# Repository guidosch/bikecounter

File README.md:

# BikeCounter  <!-- omit in toc -->

This repository contains the hardware and software components of a [PIR](https://en.wikipedia.org/wiki/Passive_infrared_sensor) based tracking device to monitor the usage of local bike trails. The data is sent over [LoRaWAN](https://de.wikipedia.org/wiki/Long_Range_Wide_Area_Network) to [TTN](https://www.thethingsnetwork.org/) and from there to a [Google Cloud](https://console.cloud.google.com) backend which stores the data and provides api endpoints for the data visualization web UI ([bikeCounterUI](https://github.com/guidosch/bikecounterUI)).

The repository is divided into two main sections. The first one contains all the data regarding the hardware components and the second one holds the software code.

- [Hardware](#hardware)
- [Software](#software)
  - [Overview](#overview)
  - [BikeCounter](#bikecounter)
    - [Overall state machine](#overall-state-machine)
    - [Data package](#data-package)
    - [Time scheduler](#time-scheduler)
    - [Device configuration](#device-configuration)
    - [Unit tests](#unit-tests)
    - [To be aware of](#to-be-aware-of)
  - [TTN](#ttn)
  - [Google Cloud](#google-cloud)
- [Contributing](#contributing)
- [License](#license)

# Hardware

The core component of the device is an [Arduino MRKWAN 1310](https://docs.arduino.cc/hardware/mkr-wan-1310) which sits on the "logic layer" PCB. This PCB connects the micro controller to the sensors, the dip switches and the "power layer" PCB.

To detect the movement a PIR sensor from [Seeed Studio](https://www.seeedstudio.com/Grove-PIR-Motion-Sensor.html) is used and to monitor the internal environment of the device a temperature and humidity sensor from [Adafruit](https://www.adafruit.com/product/3721) was chosen.

The "power layer" PCB holds two rechargeable lithium-ion batteries (18650). This allows the device to run up to one year without exchanging the batteries.

The schematics and layout files of the PCBs as well as the BOM of the whole device can be found in the corresponding subfolder.

# Software

This Repository contains the code for the tracking device as well as the scripts running on the backend.

## Overview

```mermaid
flowchart LR;
  subgraph BikeCounter;
    Biker(Round) -->|infrared radiation| PIR-sensor;
    PIR-sensor -->|DIO| Arduino-MKRWAN-1310;
    Temp&Hum-sensor -->|I2C| Arduino-MKRWAN-1310;
    DIP-switches -->|DIO| Arduino-MKRWAN-1310;
  end; 
  subgraph TTN;   
    Arduino-MKRWAN-1310 -->|LoRaWAN| PayloadFormatter;
  end;  
  subgraph Google Cloud;
    PayloadFormatter -->|webhook| Cloud-function;
    Cloud-function --> firebase;
  end;
```

## BikeCounter

There are two versions of the main BikeCounter software. The **light** version is a simple and basic implementation of the needed functionality. The **pro** version has extended features that allow it to take track of time as well as its environnement conditions.

(Due to the fact that the light version is almost obsolete only the pro version will be explained in more detail.)

### Overall state machine

```mermaid
stateDiagram-v2
    m1: main loop
    [*] --> Setup
    Setup --> m1
    state m1 {
      state if_motion <<choice>>
      s0: motion detected ?
      s1: store information in variable      
      s2: timer called
      s3: threshold reached ?
      state if_threshold <<choice>>
      s4: send data
      state if_downlink <<choice>>
      s5: downlink received ?
      s6: correct rtc drift
      
      [*] --> s0
      s0 --> if_motion
      if_motion --> s1: true
      if_motion --> s2: false
      s2 --> s4
      s1 --> s3
      s3 --> if_threshold
      if_threshold --> deepSleep: false
      if_threshold --> s4: true
      s4 --> s5
      s5 --> if_downlink
      if_downlink --> deepSleep: false
      if_downlink --> s6: true
      s6 --> deepSleep
      deepSleep --> [*]
    }
```

After the main loop finishes the device goes into a deepSleep mode. From there the PIR sensor or the rtc timer can wake it back up and trigger the main loop again.

### Data package

The payload size of one single LoRaWAN data package is restricted to 51 bytes. To avoid multi-package messages and to reduce transmission time an optimized information transmission protocol was developed.

The dataPackage class handles all the information conversion and encoding. A detailed documentation of the protocol can be found in the dataPackage.xlsx file.

**Payload encoding**

| address<br>bits | 0-7<br>[8] | 8-11<br>[4]      | 12-15<br>[4]     | 16-18<br>[3] | 19-23<br>[5]    | 24-27<br>[5] | 28-30<br>[3] | 31-54<br>[24] | 55-57<br>[3]   | 58-62<br>[5]    | 63-408<br>[6/7/8/9/10] |
| --------------- | ---------- | ---------------- | ---------------- | ------------ | --------------- | ------------ | ------------ | ------------- | -------------- | --------------- | ---------------------- |
| **content**     | count      | software version | hardware version | status index | battery voltage | temperature  | humidity     | device time   | interval index | hour of the day | offset minutes array   |

The data type size of the offset array depends on the selected interval.

### Time scheduler

During the night as well as the cold seasons of the year the data transmission interval can be adjusted to save energy and transmission time. The timeScheduler class provides all the necessary methods to accomplish such a dynamic behavior.

### Device configuration

The configuration information to establish a connection to the TTN (AppEUI and AppKey) is saved to the flash memory of the Arduino MKRWAN 1310. The `writeConfigToFlash.ino` script saves a new configuration to the memory.

### Unit tests

This repository contains serval unit tests for the dataPackage and the timeScheduler class. The tests are written using the [Google Test](https://google.github.io/googletest/) framework. A cMake configuration for local testing is provided as well as an automated CI pipeline for the master branch. The `runTestsLocal.sh` script executes all the commands needed to run the unit tests locally.

### To be aware of

- The LoRa module is very timing sensitive. That is the reason there are so many delays in the code to give it enough time to wait for messages and to response.

- The first time the (deep)sleep method is called, it re-initializes the RTC to a wrong value. To fix this issue the first iteration of the main loop puts the device into the sleep mode for a short period of time and resets the RTC in the next loop.

## TTN

The message from the device gets over LoRaWAN to the TTN server where a uplink payload formatter parses the data bytes to a human readable JavaScript object. The server then triggers a webhook and passes the data object to the Google Cloud function API endpoint.

The downlink message with the time drift information will also be parsed by the payload formatter defined in TTN.

The up/down-link payload formatter scripts are stored in the TTN subfolder.

## Google Cloud

The triggered cloud function evaluates the data object sent from TTN and saves it to the Firebase database. Depending on the difference between the local time of the device and the server time it schedules a downlink message to correct the internal device time.

There are also cloud functions that provide an API endpoint for the web UI ([bikeCounterUI](https://github.com/guidosch/bikecounterUI)) to visualize the stored data.

# Setup IDE and compile code
Download and install: `arduino-cli` which is available for brew or apt-get. Install the `arduino` extension for VSCode and adjust the `arduino.path` in the extension settings and point to your arduino-cli installation folder.

Add the following libraries to your installation: `arduino-cli lib install [libName]`

- Needed libraries:
  - MKRWAN@1.1.0
  - RTCZero@1.6.0
  - SPI.h --> already preinstalled
  - SparkFun SPI SerialFlash Arduino Library@1.0.3
  - Arduino Low Power@1.2.2
  - Adafruit Unified Sensor@1.1.6

Copy and adjust the `.vscode/c_cpp_properties.json_example` for your platform. You have to adjust the place where arduino-cli downloads the libraries as they are needed by the IDE

Compile: `arduino-cli compile --fqbn arduino:samd:mkrwan1310 BikeCounterPro.ino`

Deploy: `arduino-cli upload -p [/dev/yourdevice] --fqbn arduino:samd:mkrwan1310 BikeCounterPro.ino`

Hint: `arduino-cli board list` will show the USB port, where the device is connected

# Contributing

Pull requests are welcome. For major changes, please open an issue first to discuss what you would like to change.

Please make sure to update the tests as appropriate.

# License

This project is licensed under [CC0-1.0](LICENSE)

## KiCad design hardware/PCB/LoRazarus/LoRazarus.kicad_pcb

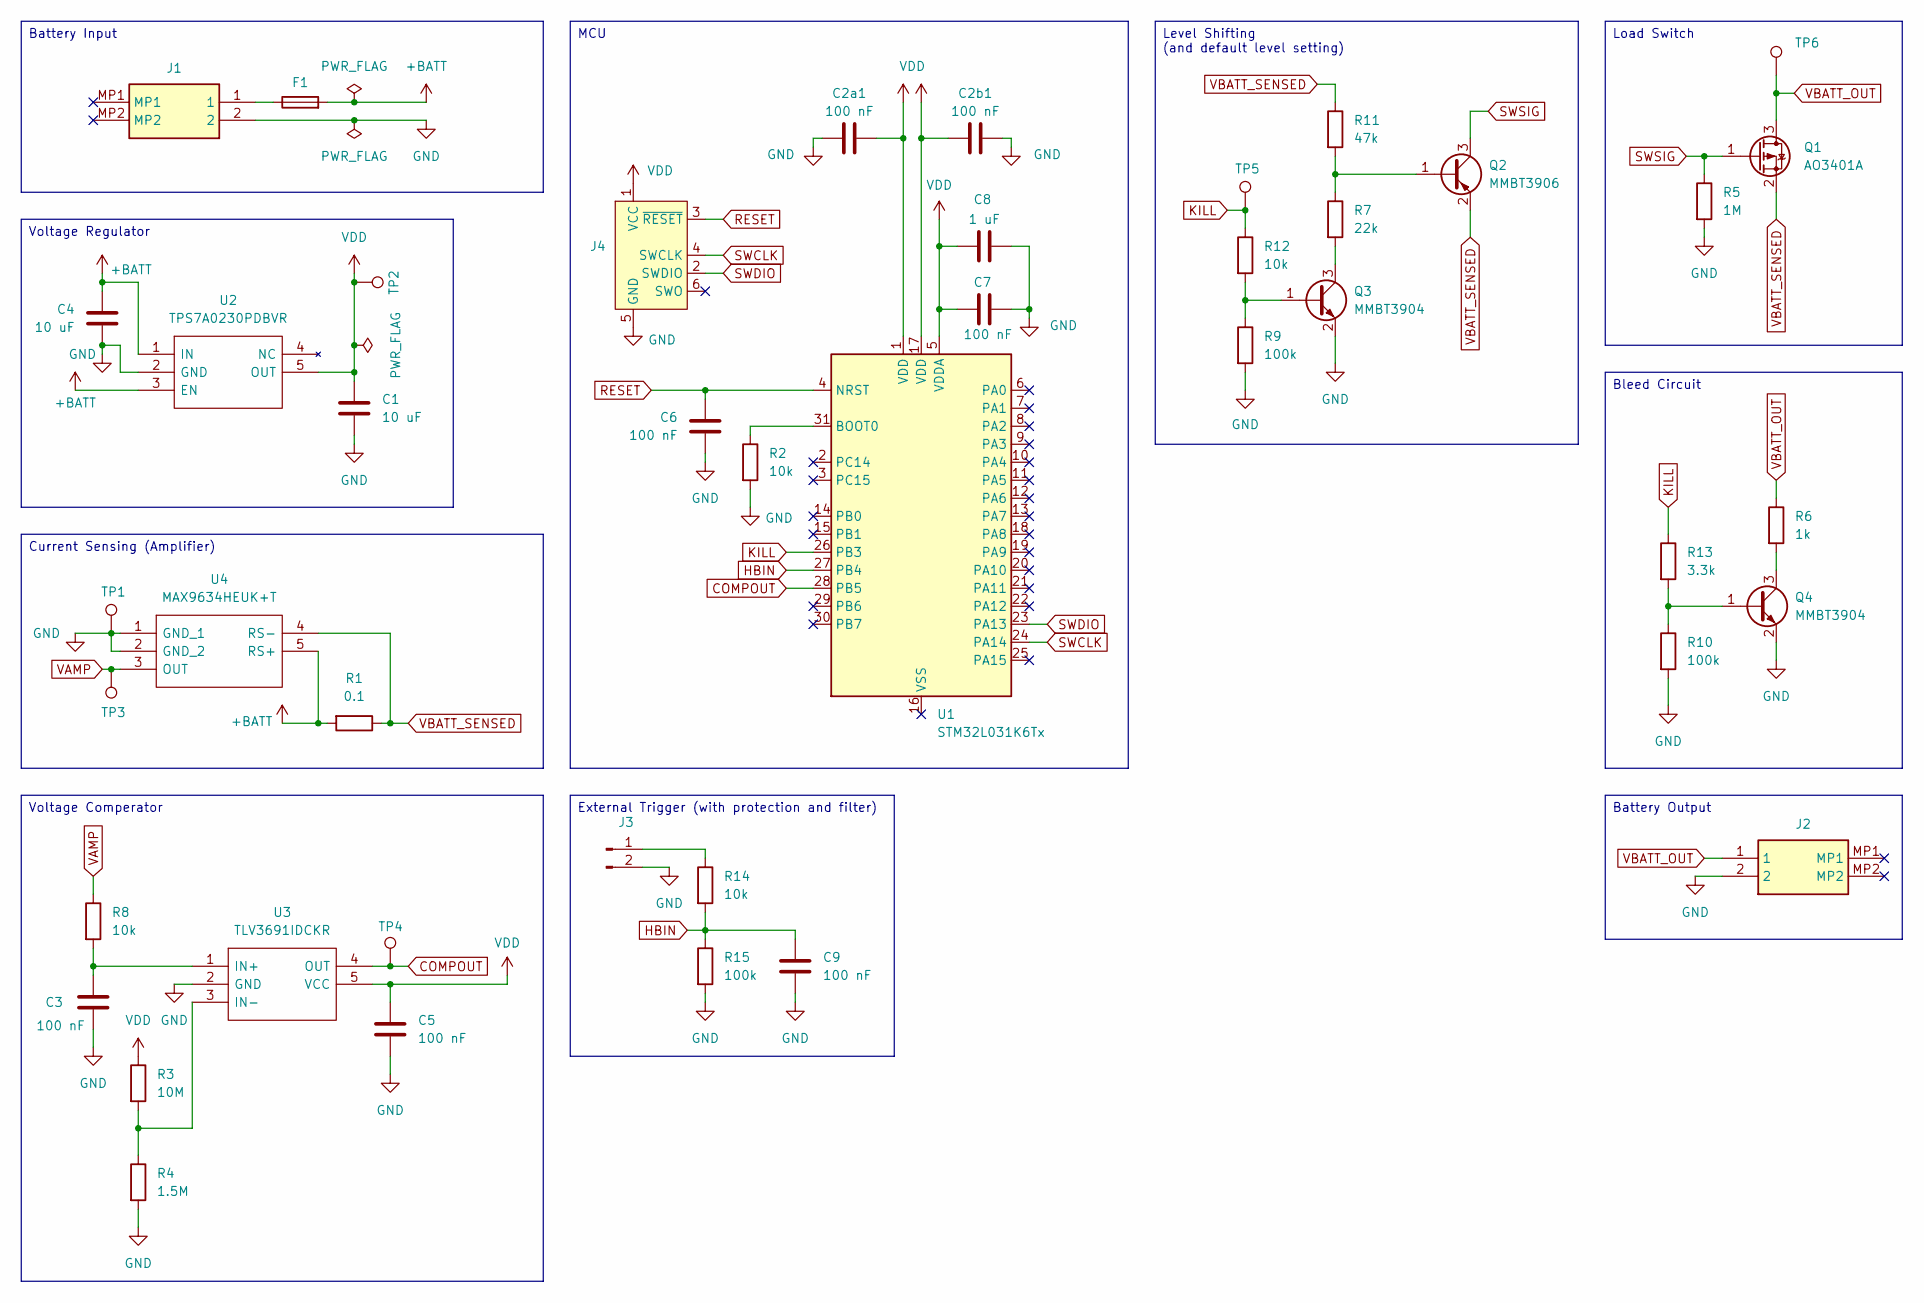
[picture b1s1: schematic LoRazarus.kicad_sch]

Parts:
C1, C4: 10 uF; C_0805_2012Metric
C2a1, C2b1, C3, C5, C6, C7, C9: 100 nF; C_0603_1608Metric
C8: 1 uF; C_0603_1608Metric
F1: Fuse; Fuse_1206_3216Metric
J1, J2: S2B-PH-SM4-TB_LF__SN_; S2BPHSM4TBLFSN; Mouser Part Number N/A
J3: Conn_01x02_Pin; PinHeader_1x02_P2.54mm_Vertical
J4: Conn_ARM_SWD_TagConnect_TC2030-NL; Tag-Connect_TC2030-IDC-NL_2x03_P1.27mm_Vertical
Q1: AO3401A; SOT-23
Q2: MMBT3906; SOT-23
Q3, Q4: MMBT3904; SOT-23
R1: 0.1; R_1206_3216Metric
R2, R8, R12, R14: 10k; R_0603_1608Metric
R3: 10M; R_0603_1608Metric
R4: 1.5M; R_0603_1608Metric
R5: 1M; R_0603_1608Metric
R6: 1k; R_0603_1608Metric
R7: 22k; R_0603_1608Metric
R9, R10, R15: 100k; R_0603_1608Metric
R11: 47k; R_0603_1608Metric
R13: 3.3k; R_0603_1608Metric
TP1, TP2, TP3, TP4, TP5, TP6: TestPoint; TestPoint_Pad_1.0x1.0mm
U1: STM32L031K6Tx; LQFP-32_7x7mm_P0.8mm
U2: TPS7A0230PDBVR; SOT-23-5; Mouser Part Number 595-TPS7A0230PDBVR
U3: TLV3691IDCKR; SOT-353_SC-70-5; Mouser Part Number 595-TLV3691IDCKR
U4: MAX9634HEUK+T; SOT-23-5; Mouser Part Number 700-MAX9634HEUKT

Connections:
+BATT: C4.1, F1.2, R1.2, U2.1 (IN), U2.3 (EN), U4.5 (RS+)
COMPOUT: TP4.1 (1_1), U1.28 (PB5), U3.4 (OUT)
GND: C1.2, C2a1.2, C2b1.2, C3.2, C4.2, C5.2, C6.2, C7.2, C8.2, C9.2, J1.2, J2.2, J3.2, J4.5 (GND), Q3.2 (E), Q4.2 (E), R2.2, R4.2, R5.2, R9.2, R10.2, R15.2, TP1.1 (1_1), U2.2 (GND), U3.2 (GND), U4.1 (GND_1), U4.2 (GND_2)
HBIN: C9.1, R14.2, R15.1, U1.27 (PB4)
KILL: R12.1, R13.1, TP5.1 (1_1), U1.26 (PB3)
unnamed: F1.1, J1.1
unnamed: J3.1, R14.1
unnamed: Q2.1 (B), R7.1, R11.2
unnamed: Q3.1 (B), R9.1, R12.2
unnamed: Q3.3 (C), R7.2
unnamed: Q4.1 (B), R10.1, R13.2
unnamed: Q4.3 (C), R6.2
unnamed: R2.1, U1.31 (BOOT0)
unnamed: C3.1, R8.2, U3.1 (IN+)
unnamed: R3.2, R4.1, U3.3 (IN-)
RESET: C6.1, J4.3 (~RESET), U1.4 (NRST)
SWCLK: J4.4 (SWCLK), U1.24 (PA14)
SWDIO: J4.2 (SWDIO), U1.23 (PA13)
SWSIG: Q1.1 (G), Q2.3 (C), R5.1
VAMP: R8.1, TP3.1 (1_1), U4.3 (OUT)
VBATT_OUT: J2.1, Q1.3 (D), R6.1, TP6.1 (1_1)
VBATT_SENSED: Q1.2 (S), Q2.2 (E), R1.1, R11.1, U4.4 (RS-)
VDD: C1.1, C2a1.1, C2b1.1, C5.1, C7.1, C8.1, J4.1 (VCC), R3.1, TP2.1 (1_1), U1.1 (VDD), U1.5 (VDDA), U1.17 (VDD), U2.5 (OUT), U3.5 (VCC)

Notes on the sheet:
Battery Input
External Trigger (with protection and filter)
Battery Output
Load Switch
Voltage Regulator
Level Shifting (and default level setting)
Current Sensing (Amplifier)
MCU
Bleed Circuit
Voltage Comperator

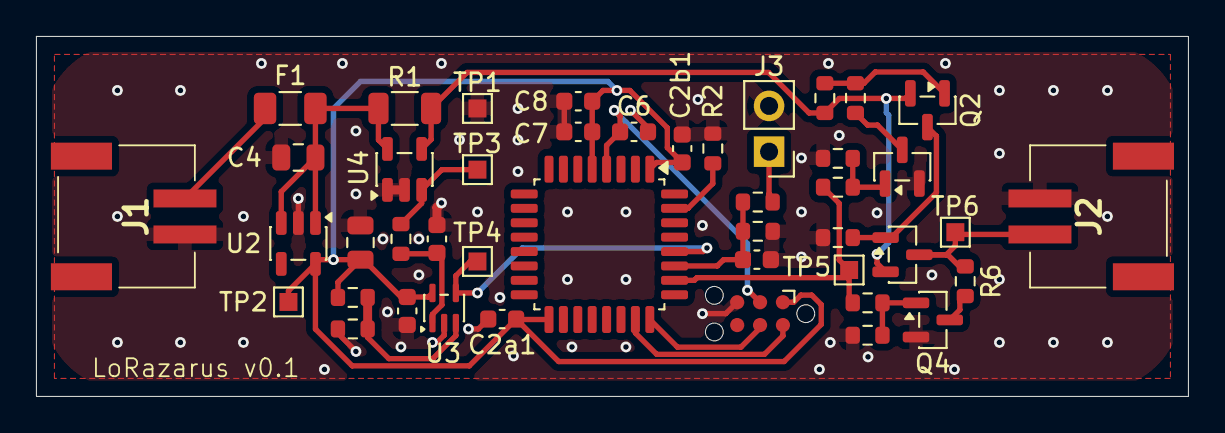
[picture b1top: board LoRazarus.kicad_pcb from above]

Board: 2 copper layers, 64.0 x 20.0 mm, 44 parts (0 on the bottom side), 23 nets.

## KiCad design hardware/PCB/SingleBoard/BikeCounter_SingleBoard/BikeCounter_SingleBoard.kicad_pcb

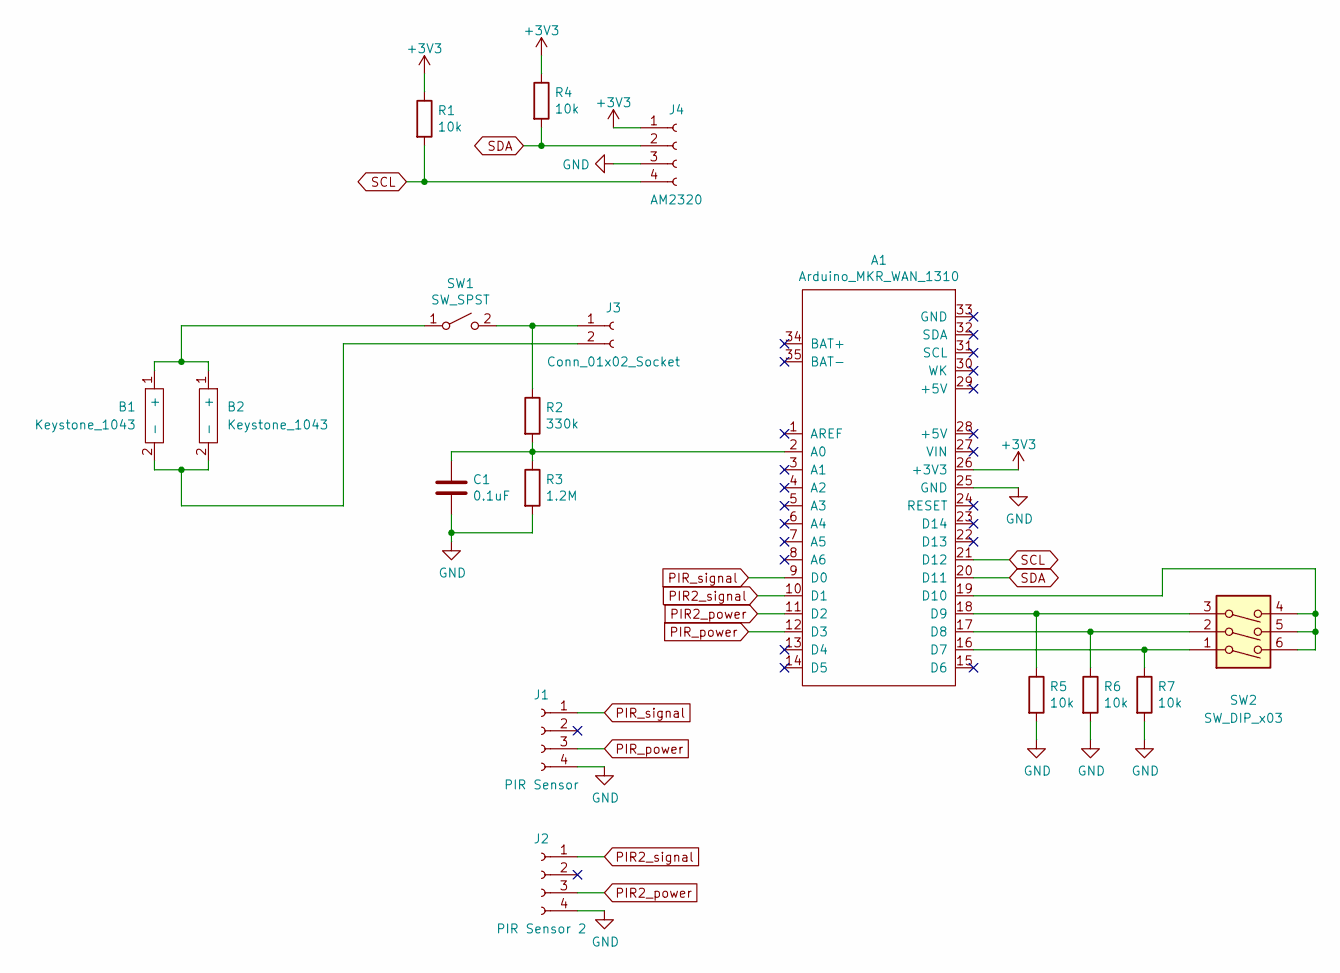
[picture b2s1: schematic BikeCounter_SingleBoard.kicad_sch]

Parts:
A1: Arduino_MKR_WAN_1310
B1, B2: Keystone_1043; BatteryHolder_Keystone_1043_1x18650
C1: 0.1uF; C_0805_2012Metric_Pad1.18x1.45mm_HandSolder
J1: PIR Sensor; PinSocket_1x04_P2.00mm_Vertical
J2: PIR Sensor 2; PinSocket_1x04_P2.00mm_Vertical
J3: Conn_01x02_Socket; PinSocket_1x02_P2.54mm_Vertical
J4: AM2320; PinSocket_1x04_P2.54mm_Vertical
R1, R4, R5, R6, R7: 10k; R_1206_3216Metric_Pad1.30x1.75mm_HandSolder
R2: 330k; R_1206_3216Metric_Pad1.30x1.75mm_HandSolder
R3: 1.2M; R_1206_3216Metric_Pad1.30x1.75mm_HandSolder
SW1: SW_SPST; Switch_MHS12204
SW2: SW_DIP_x03; SW_DIP_SPSTx03_Slide_6.7x9.18mm_W8.61mm_P2.54mm_LowProfile

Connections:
+3V3: A1.26 (+3V3), J4.1, R1.1, R4.1
GND: A1.25 (GND), C1.2, J1.4, J2.4, J4.3, R3.2, R5.2, R6.2, R7.2
unnamed: A1.2 (A0), C1.1, R2.2, R3.1
unnamed: A1.16 (D7), R7.1, SW2.1
unnamed: A1.17 (D8), R6.1, SW2.2
unnamed: A1.18 (D9), R5.1, SW2.3
unnamed: A1.19 (D10), SW2.4, SW2.5, SW2.6
unnamed: B1.1 (+), B2.1 (+), SW1.1 (A)
unnamed: B1.2 (-), B2.2 (-), J3.2
unnamed: J3.1, R2.1, SW1.2 (B)
PIR2_power: A1.11 (D2), J2.3
PIR2_signal: A1.10 (D1), J2.1
PIR_power: A1.12 (D3), J1.3
PIR_signal: A1.9 (D0), J1.1
SCL: A1.21 (D12), J4.4, R1.2
SDA: A1.20 (D11), J4.2, R4.2

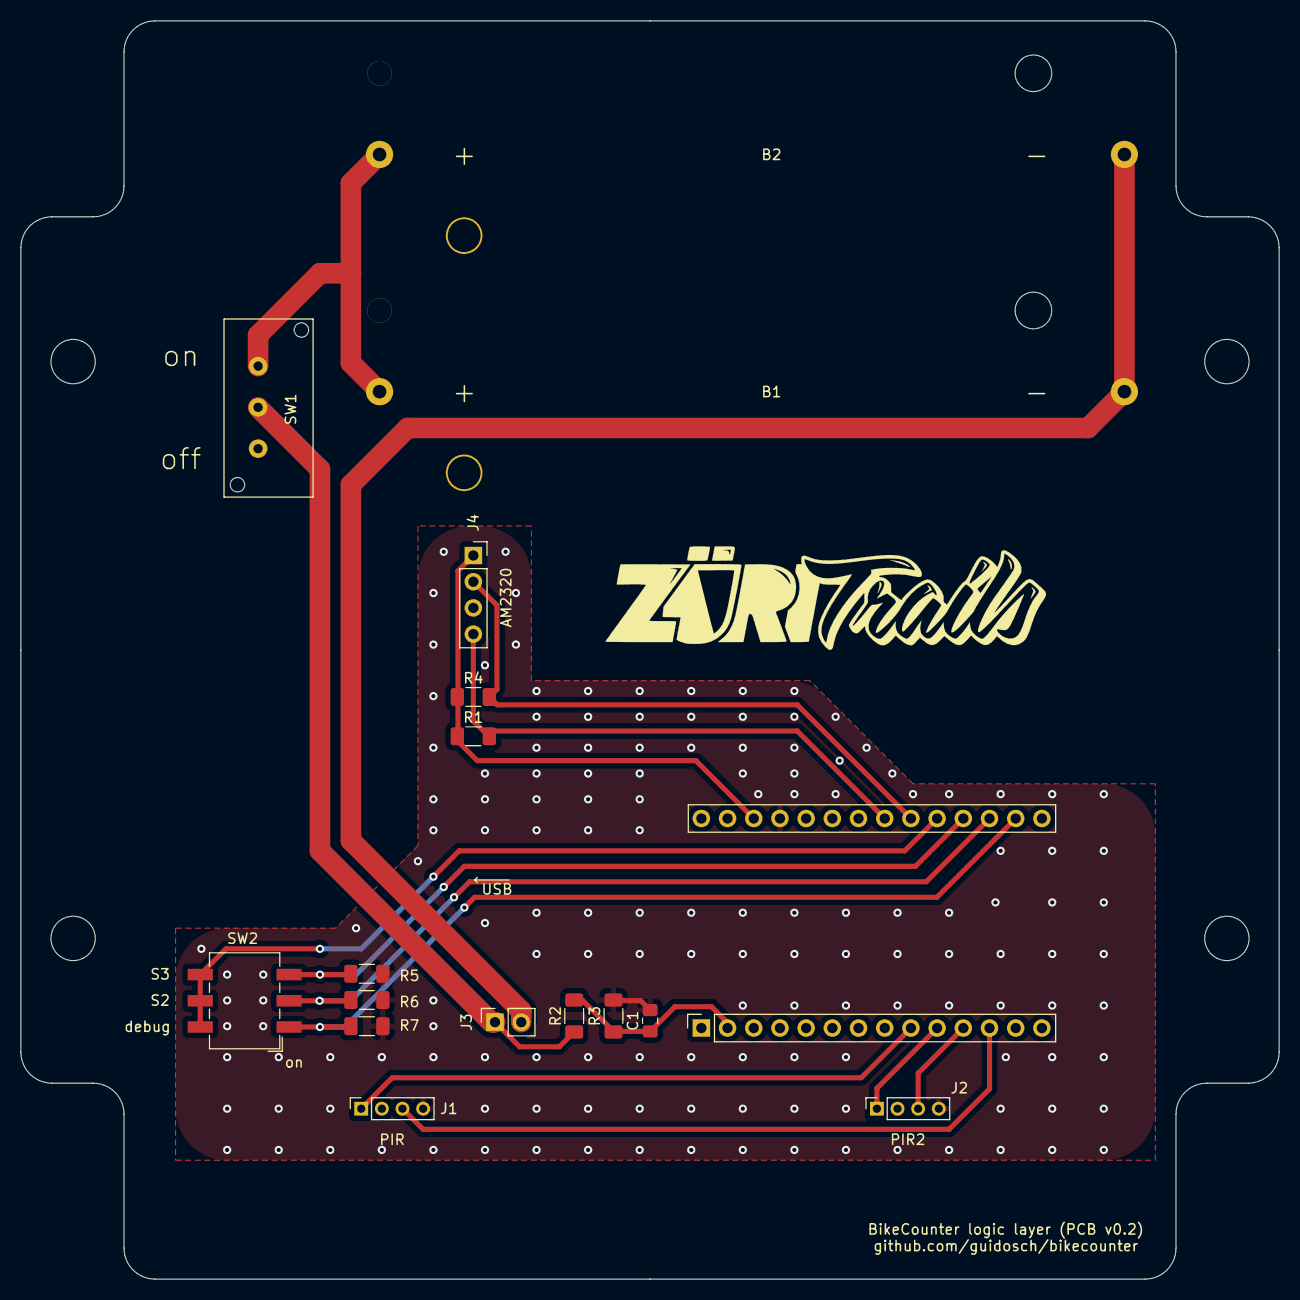
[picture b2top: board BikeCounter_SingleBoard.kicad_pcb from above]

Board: 2 copper layers, 122.0 x 122.0 mm, 17 parts (0 on the bottom side), 16 nets.

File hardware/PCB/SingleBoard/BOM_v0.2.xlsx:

Id | Designator | Package | Quantity | Designation | Price |  | Link 1 | Link 2 | Link 3
1 |  | PCB | 1 | JLC PCB (20 Stk.) | 3.5590000000000002 | 3.5590000000000002
2 | A1 | Arduino_MKR_WAN_1310 | 1 | Arduino_MKR_WAN_1310 | 39.44 | 39.44 | https://www.mouser.ch/ProductDetail/Arduino/ABX00029?qs=rkhj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
3 | B1,B2 | BatteryHolder_Keystone_1043_1x18650 | 2 |  | 2.15 | 4.3 | https://www.mouser.ch/ProductDetail/Keystone-Electronics/104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
 | C1 | Capacitor_SMD:C_0805_2012Metric_Pad1.18x1.45mm_HandSolder | 2 | 0.1uF | 5.6000000000000001E-2 | 0.112 | https://www.mouser.ch/ProductDetail/KEMET/C0805C104K5RAC7411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 | https://www.mouser.ch/ProductDetail/Murata-Electronics/GCJ31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
 | R1,R4,R5,R6,R7 | Resistor_SMD:R_1206_3216Metric_Pad1.30x1.75mm_HandSolder | 5 | 10k | 0.186 | 0.92999999999999994 | https://www.mouser.ch/ProductDetail/Bourns/CHP1206AFX-1002EL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
 | R2 | Resistor_SMD:R_1206_3216Metric_Pad1.30x1.75mm_HandSolder | 1 | 330k | 0.121 | 0.121 | https://www.mouser.ch/ProductDetail/Susumu/RG3216P-3303-D-T5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
 | R3 | Resistor_SMD:R_1206_3216Metric_Pad1.30x1.75mm_HandSolder | 1 | 1.2M | 0.14199999999999999 | 0.14199999999999999 | https://www.mouser.ch/ProductDetail/YAGEO/RT1206FRE071M2L?qs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
 | SW1 | General_TM:Switch_MHS12204 | 1 | SW_SPST | 0.72799999999999998 | 0.72799999999999998 | https://www.mouser.ch/ProductDetail/TE-Connectivity-Alcoswit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
 | SW2 | Button_Switch_SMD:SW_DIP_SPSTx03_Slide_6.7x9.18mm_W8.61mm_P2.54mm_LowProfile | 1 | SW_DIP_x03 | 0.51200000000000001 | 0.51200000000000001 | https://www.mouser.ch/ProductDetail/CTS-Electronic-Component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
 | J1,J2 | Connector_PinSocket_2.00mm:PinSocket_1x04_P2.00mm_Vertical | 2 | PIR, PIR 2 | 9.9000000000000005E-2 | 0.19800000000000001 | https://www.seeedstudio.com/Grove-Universal-4-pin-connector.html
 |  | PinSocket_1x14_P2.54mm_Vertical | 2 | Board connector | 1.93 | 3.86 | https://www.mouser.ch/ProductDetail/Harwin/M20-7821446?qs=Jp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
 |  | Grove PIR sensor | 1 |  | 7.06 | 7.06 | https://www.distrelec.ch/de/grove-pir-bewegungssensor-seeed-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
 |  | AM2320 | 1 |  | 6.65 | 6.65 | https://www.distrelec.ch/de/digitaler-temperatur-und-feuchti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
 |  | Antenne | 1 |  | 21.52 | 21.52 | https://www.mouser.ch/ProductDetail/712-ANT-8-9-SPNF2
 |  | Adapter | 1 |  | 15.23 | 15.23 | https://www.mouser.ch/ProductDetail/523-242114
 |  | Kabel | 1 |  | 8.1 | 8.1 | https://www.mouser.ch/ProductDetail/RF-Solutions/CBA-UFLSMA1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
 |  | Casing 135x135x60mm | 1 |  | 18.5 | 18.5 | https://www.distrelec.ch/de/kunststoffgehaeuse-mit-durchsich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
 |  | Schrauben M3.5 | 4 |  | 1.2500000000000001E-2 | 0.05 | https://www.distrelec.ch/de/kreuzschraube-flachkopf-blech-po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
 |  | Akku | 2 | 2.6Ah | 18.32 | 36.64 | https://www.distrelec.ch/de/akku-li-ion-18650-6v-6ah-ansmann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
 |  |  |  |  |  | 164.09300000000002
 |  | Akku alternative | 1 | 3.5Ah | 23.32 | 23.32 | https://www.distrelec.ch/de/akku-li-ion-18650-6v-5ah-ansmann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
 |  | Akku alternative | 1 | 3.4Ah (USB ladebuchse) | 21.9 | 21.9 | https://www.distrelec.ch/de/akku-mit-usb-ladebuchse-li-ion-1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
 |  |  |  | Aufstellung für 5 Stück | 746.96500000000015
 |  |  |  | Aufstellung für 10 Stück | 1567.4300000000003

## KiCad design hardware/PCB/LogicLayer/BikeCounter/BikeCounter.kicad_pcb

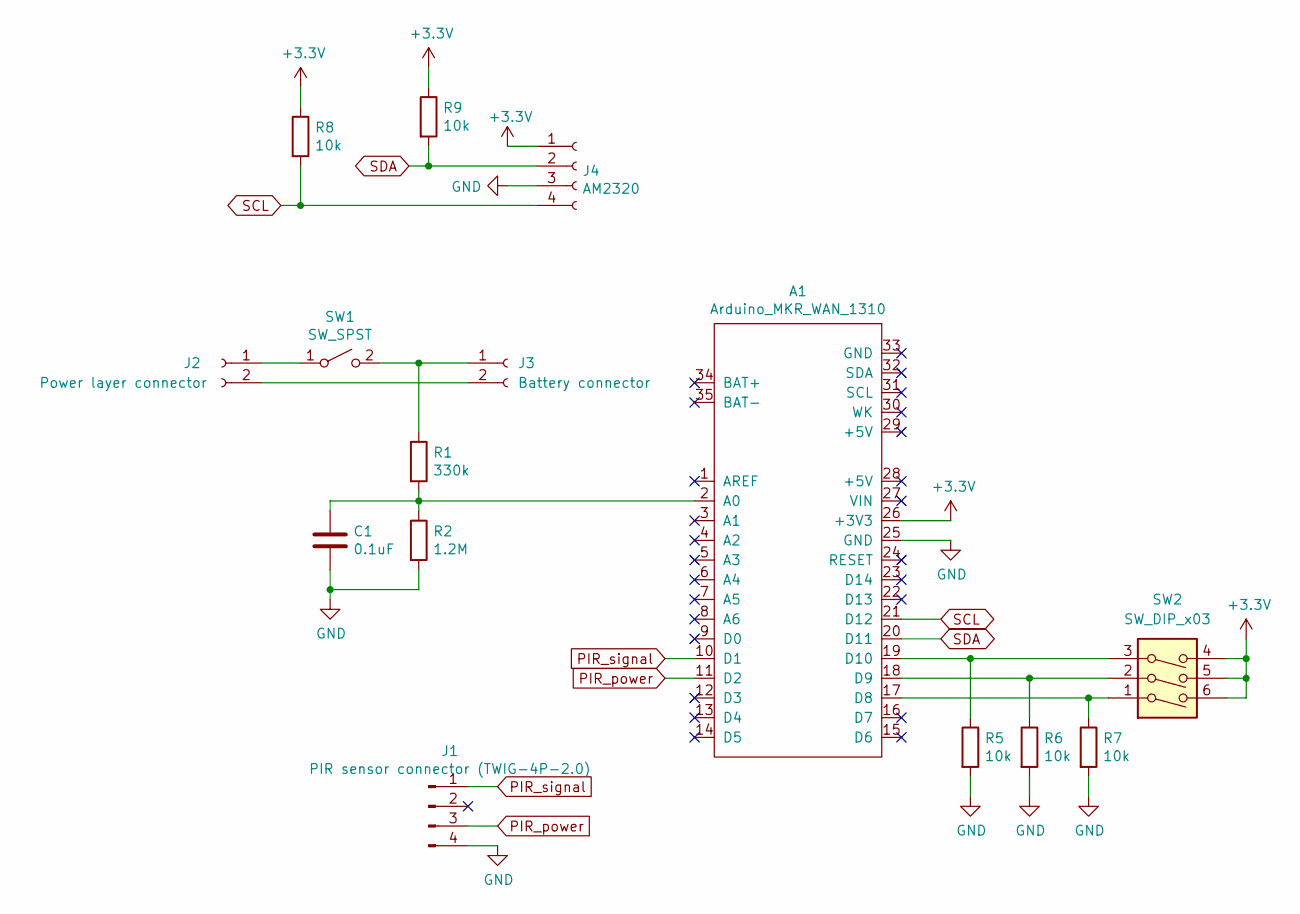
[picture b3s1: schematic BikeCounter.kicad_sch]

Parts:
A1: Arduino_MKR_WAN_1310
C1: 0.1uF; C_0805_2012Metric_Pad1.18x1.45mm_HandSolder
J1: PIR sensor connector (TWIG-4P-2.0); PinSocket_1x04_P2.00mm_Vertical
J2: Power layer connector; PinSocket_1x02_P2.54mm_Vertical
J3: Battery connector; PinSocket_1x02_P2.54mm_Vertical
J4: AM2320; PinSocket_1x04_P2.54mm_Vertical
R1: 330k; R_1206_3216Metric_Pad1.30x1.75mm_HandSolder
R2: 1.2M; R_1206_3216Metric_Pad1.30x1.75mm_HandSolder
R5, R6, R7, R8, R9: 10k; R_1206_3216Metric_Pad1.30x1.75mm_HandSolder
SW1: SW_SPST; Switch_MHS12204
SW2: SW_DIP_x03; SW_DIP_SPSTx03_Slide_6.7x9.18mm_W8.61mm_P2.54mm_LowProfile

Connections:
+3V3: A1.26 (+3V3), J4.1, R8.1, R9.1, SW2.4, SW2.5, SW2.6
GND: A1.25 (GND), C1.2, J1.4, J4.3, R2.2, R5.2, R6.2, R7.2
unnamed: A1.2 (A0), C1.1, R1.2, R2.1
unnamed: A1.17 (D8), R7.1, SW2.1
unnamed: A1.18 (D9), R6.1, SW2.2
unnamed: A1.19 (D10), R5.1, SW2.3
unnamed: J2.1, SW1.1 (A)
unnamed: J2.2, J3.2
unnamed: J3.1, R1.1, SW1.2 (B)
PIR_power: A1.11 (D2), J1.3
PIR_signal: A1.10 (D1), J1.1
SCL: A1.21 (D12), J4.4, R8.2
SDA: A1.20 (D11), J4.2, R9.2

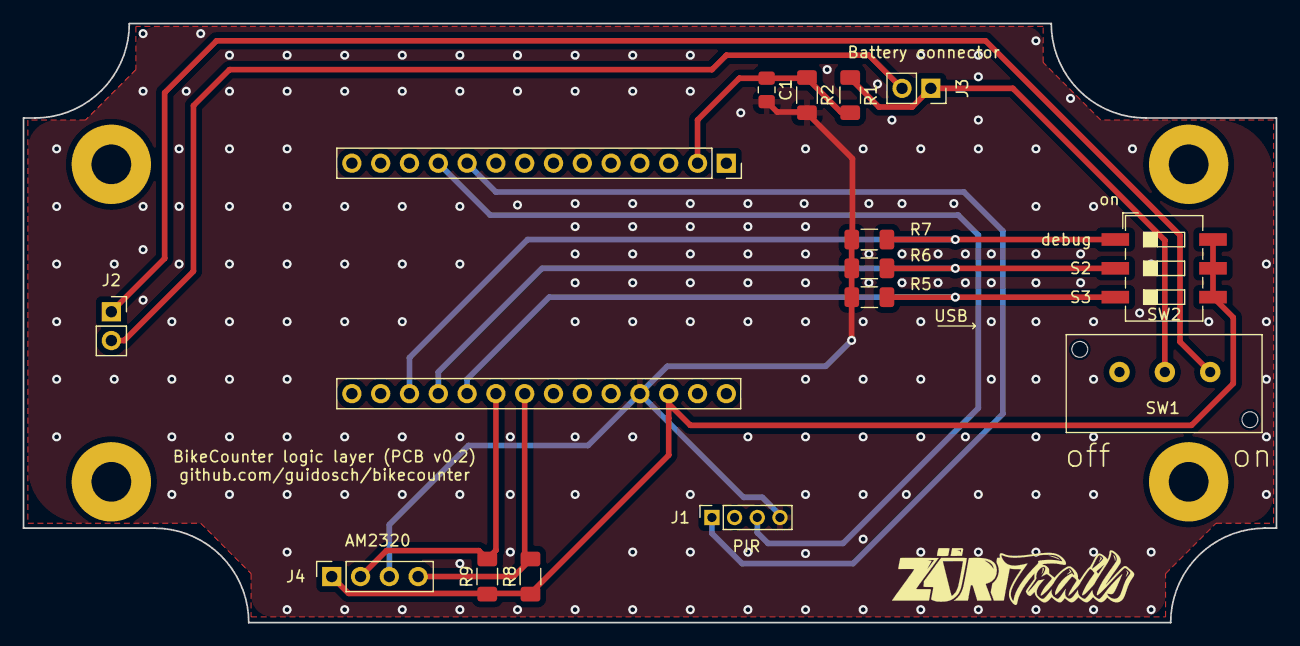
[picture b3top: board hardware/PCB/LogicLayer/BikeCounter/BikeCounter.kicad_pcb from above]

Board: 2 copper layers, 110.5 x 52.8 mm, 15 parts (0 on the bottom side), 13 nets.

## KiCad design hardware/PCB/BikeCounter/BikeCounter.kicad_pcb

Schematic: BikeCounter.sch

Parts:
A1: Arduino_MKR_WAN_1310
BT1: Battery_Cell; BatteryHolder_Keystone_1042_1x18650
BT2: Battery_Cell; BatteryHolder_Keystone_3000_1x12mm
C1, C3: 0.1uF; C_0805_2012Metric_Pad1.15x1.40mm_HandSolder
C2: 10uF; C_1206_3216Metric_Pad1.33x1.80mm_HandSolder
J1: PIR sensor connector (TWIG-4P-2.0); PinSocket_1x04_P2.00mm_Vertical
J2: Conn_01x04_Female; PinSocket_1x04_P2.54mm_Vertical
J3: Conn_01x02_Female; PinSocket_1x02_P2.54mm_Vertical
R1: 330k; R_1206_3216Metric_Pad1.42x1.75mm_HandSolder
R2: 1.2M; R_1206_3216Metric_Pad1.42x1.75mm_HandSolder
R3, R4, R5, R6, R7: 10k; R_1206_3216Metric_Pad1.42x1.75mm_HandSolder
SW1: SW_DIP_x03; SW_DIP_SPSTx03_Slide_6.7x9.18mm_W8.61mm_P2.54mm_LowProfile
U1: DS3231M; SOIC-16W_7.5x10.3mm_P1.27mm

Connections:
+3V3: A1.26 (+3V3), C2.1, C3.1, J1.3, J2.2, R3.1, R4.1, SW1.4, SW1.5, SW1.6, U1.2 (VCC)
+3V8: BT1.1 (+), J3.1, R1.1
GND: A1.25 (GND), BT1.2 (-), BT2.2 (-), C1.2, C2.2, C3.2, J1.4, J2.1, J3.2, R2.2, R5.2, R6.2, R7.2, U1.5 (GND), U1.6 (GND), U1.7 (GND), U1.8 (GND), U1.9 (GND), U1.10 (GND), U1.11 (GND), U1.12 (GND), U1.13 (GND)
unnamed: A1.2 (A0), C1.1, R1.2, R2.1
unnamed: A1.17 (D8), R7.1, SW1.3
unnamed: A1.18 (D9), R6.1, SW1.2
unnamed: A1.19 (D10), R5.1, SW1.1
unnamed: BT2.1 (+), U1.14 (VBAT)
PIR_signal: A1.10 (D1), J1.1
RTC_32KHZ: J2.4, U1.1 (32KHZ)
RTC_RST: J2.3, U1.4 (~RST)
RTC_timer: A1.9 (D0), U1.3 (~INT~/SQW)
SCL: A1.21 (D12), R4.2, U1.16 (SCL)
SDA: A1.20 (D11), R3.2, U1.15 (SDA)

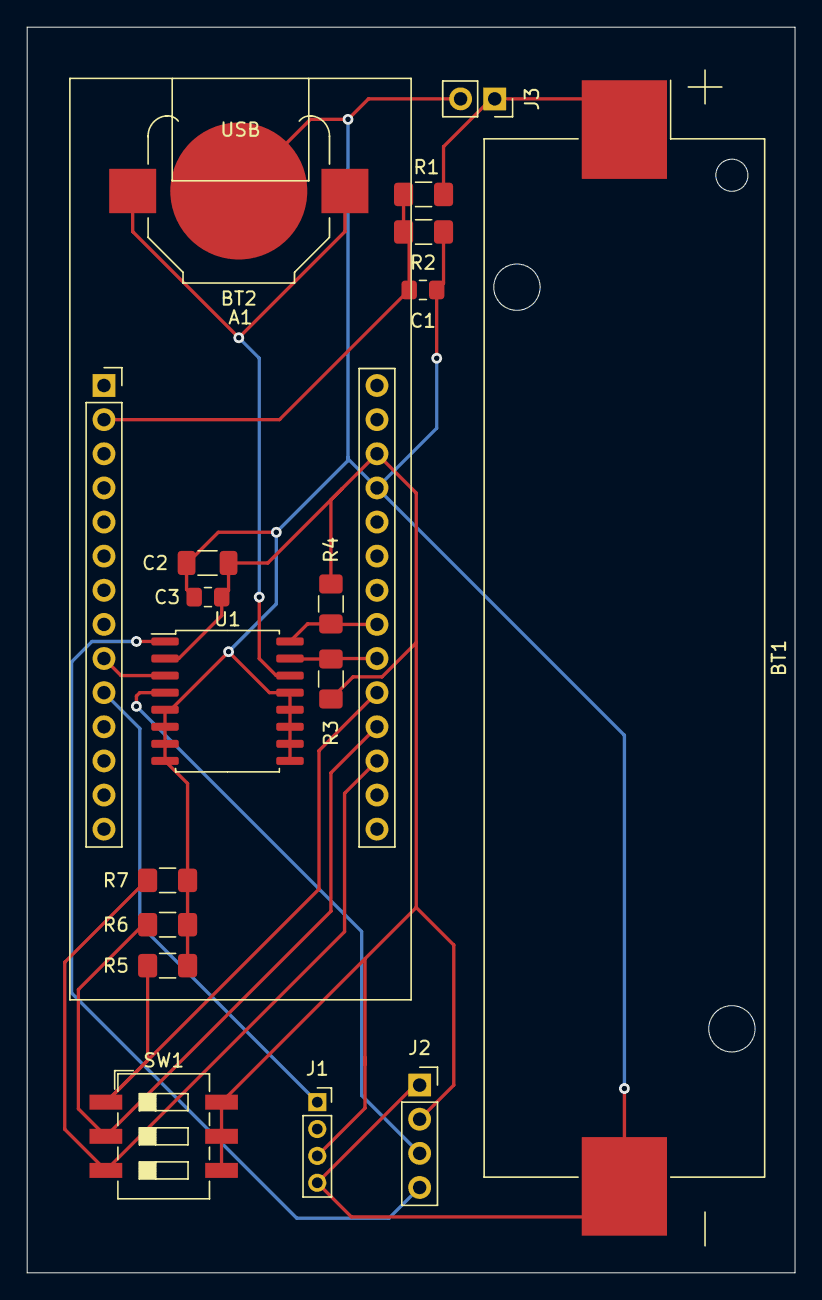
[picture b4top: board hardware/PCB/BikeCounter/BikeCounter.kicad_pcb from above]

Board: 2 copper layers, 57.2 x 92.7 mm, 18 parts (0 on the bottom side), 14 nets.

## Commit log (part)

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2020-03-07 Initial version with upload functions and chart for bikecounter.
2020-03-08 Added visualization for heatpump data.
2020-03-22 Added Adlisbertrail title
2020-03-28 Fixed syntax error.
2020-03-31 More margin for buttons
2020-04-05 Allow to select trail with dropdown.
2020-05-03 Added kellerV21 data to firebase and html UI.
2020-05-08 Added css styles to heatpump monitor.
2020-05-19 Small improvements.
2020-05-23 Better styling and some date improvements
2020-06-04 Typo
2020-06-07 Bump websocket-extensions from 0.1.3 to 0.1.4
    Bumps [websocket-extensions](https://github.com/faye/websocket-extensions-node) from 0.1.3 to 0.1.4.
    - [Release notes](https://github.com/faye/websocket-extensions-node/releases)
    - [Changelog](https://github.com/faye/websocket-extensions-node/blob/master/CHANGELOG.md)
    - [Commits](https://github.com/faye/websocket-extensions-node/compare/0.1.3...0.1.4)
2020-06-25 Cooling if diff 1.5 C and forward T below 20.
2020-06-30 Added custom and fixed colors for timeline.
2020-07-19 Bump lodash from 4.17.15 to 4.17.19
    Bumps [lodash](https://github.com/lodash/lodash) from 4.17.15 to 4.17.19.
    - [Release notes](https://github.com/lodash/lodash/releases)
    - [Commits](https://github.com/lodash/lodash/compare/4.17.15...4.17.19)
2020-08-10 Bump lodash from 4.17.15 to 4.17.19 in /uploadData
    Bumps [lodash](https://github.com/lodash/lodash) from 4.17.15 to 4.17.19.
    - [Release notes](https://github.com/lodash/lodash/releases)
    - [Commits](https://github.com/lodash/lodash/compare/4.17.15...4.17.19)
2020-08-17 Cooling history was wrong
2020-08-23 Improvements to check cooling algo.
2020-09-12 Bump node-fetch from 2.6.0 to 2.6.1 in /uploadData
    Bumps [node-fetch](https://github.com/bitinn/node-fetch) from 2.6.0 to 2.6.1.
    - [Release notes](https://github.com/bitinn/node-fetch/releases)
    - [Changelog](https://github.com/node-fetch/node-fetch/blob/master/docs/CHANGELOG.md)
    - [Commits](https://github.com/bitinn/node-fetch/compare/v2.6.0...v2.6.1)
2020-09-27 Allow to switch for month to year view for all trails.
2020-12-29 Switched to async loading and some UI updates.
2021-01-29 Added Arduino sources.
2021-04-17 Value of Gratweg device was wrong.
2021-09-19 code comments added
2021-09-23 Sketches with all the different tests of the last days added (Will be deleted after final release)
2021-09-23 RTC to BikeCounterPro added
2021-09-23 battery level measurement added
2021-09-23 Solution for continous sending bug implemented
2021-09-23 Code from interrupts removed
2021-09-25 Implementation of PCF8523 finished
2021-09-25 Simpler solution for continous sending bug implemented
2021-09-26 Decoding example added
2021-09-29 appKey removed
2021-10-03 package size to data size adapted and timer interrupt improved
2021-10-03 motion interrupt improved
2021-10-05 First version of circuit diagram finished
2021-10-19 Migrated to TTN V3 payload format and added sample data.
2021-10-29 More logout in sample data parser
2021-10-29 Some more styling for html output.
2021-10-29 BikeCounterLight: floating interrupt pin detection
2021-10-30 Data package overview updated
2021-10-30 Methode to disable unused pins implemented
2021-10-31 Example skatches removed
2021-11-02 gitignore updated
2021-11-10 implemented all the recent changes of the light version into the pro version
2021-11-16 DataPackage class continued
2021-11-17 dataPackage implementation finished
2021-12-04 PowerLayer PCB batterys polarization label added
2021-12-04 Data package time array bug fixed and example decoding added
2021-12-04 CAD files generated and assembly started
2021-12-05 Payload formatter started
2021-12-05 payload formatter finished
2021-12-06 payload formatter: output time array reduced to epoch ms only
2021-12-12 STEP files renamed
2021-12-13 BOM finished and Gerber files created
2022-01-05 payload formatter and BOM updated
2022-01-09 PIR-sensor disabled during data transmission and minor spelling errors corrected
2022-01-16 time schedule class started
2022-02-03 First working versin of bikecounter UI dashboard.
2022-02-04 Removing deleted files.
2022-02-13 Bump follow-redirects from 1.12.1 to 1.14.8
    Bumps [follow-redirects](https://github.com/follow-redirects/follow-redirects) from 1.12.1 to 1.14.8.
    - [Release notes](https://github.com/follow-redirects/follow-redirects/releases)
    - [Commits](https://github.com/follow-redirects/follow-redirects/compare/v1.12.1...v1.14.8)
    ---
    updated-dependencies:
    - dependency-name: follow-redirects
2022-02-20 New version
2022-03-06 temporary RTClib mock class added
2022-03-13 BOM updated
2022-03-26 Bump minimist from 1.2.5 to 1.2.6
    Bumps [minimist](https://github.com/substack/minimist) from 1.2.5 to 1.2.6.
    - [Release notes](https://github.com/substack/minimist/releases)
    - [Commits](https://github.com/substack/minimist/compare/1.2.5...1.2.6)
    ---
    updated-dependencies:
    - dependency-name: minimist
2022-04-09 Bump moment from 2.24.0 to 2.29.2
    Bumps [moment](https://github.com/moment/moment) from 2.24.0 to 2.29.2.
    - [Release notes](https://github.com/moment/moment/releases)
    - [Changelog](https://github.com/moment/moment/blob/develop/CHANGELOG.md)
    - [Commits](https://github.com/moment/moment/compare/2.24.0...2.29.2)
    ---
    updated-dependencies:
2022-04-10 example downlink formatter added
2022-04-10 Adjusted sample data to new format.
2022-04-13 ACK flag to lora package added and RTC reset time to UTC changed
2022-04-17 Bump async from 2.6.3 to 2.6.4
    Bumps [async](https://github.com/caolan/async) from 2.6.3 to 2.6.4.
    - [Release notes](https://github.com/caolan/async/releases)
    - [Changelog](https://github.com/caolan/async/blob/v2.6.4/CHANGELOG.md)
    - [Commits](https://github.com/caolan/async/compare/v2.6.3...v2.6.4)
    ---
    updated-dependencies:
2022-04-17 Bump node-fetch from 2.6.5 to 2.6.7
    Bumps [node-fetch](https://github.com/node-fetch/node-fetch) from 2.6.5 to 2.6.7.
    - [Release notes](https://github.com/node-fetch/node-fetch/releases)
    - [Commits](https://github.com/node-fetch/node-fetch/compare/v2.6.5...v2.6.7)
    ---
    updated-dependencies:
    - dependency-name: node-fetch
2022-04-30 New version with fix of receiving time timestamp.
2022-08-01 Added startDate param to monitoring page.
2022-08-29 usage of internal rtc and device time transmission implemented
2022-09-02 time synchronization properties to payload formatter added
2022-09-02 sync call state implemented
2022-09-05 write to flash script started
2022-09-07 time sync bugs fixed
2022-09-08 appeui and app key moved to flash memory
2022-09-08 old files removed
2022-09-15 software version commit tag in DataPackage.xlsx updated
2022-09-15 .vscode files removed
2022-09-16 images added
2022-09-16 pcb image added
2022-09-16 Bump jose from 2.0.5 to 2.0.6
    Bumps [jose](https://github.com/panva/jose) from 2.0.5 to 2.0.6.
    - [Release notes](https://github.com/panva/jose/releases)
    - [Changelog](https://github.com/panva/jose/blob/v2.0.6/CHANGELOG.md)
    - [Commits](https://github.com/panva/jose/compare/v2.0.5...v2.0.6)
    ---
    updated-dependencies:
2022-09-18 google cloud functions added
2022-09-19 readme finished
2022-09-19 Bump lodash from 4.17.15 to 4.17.21 in /software/GoogleCLoud/printGraph
    Bumps [lodash](https://github.com/lodash/lodash) from 4.17.15 to 4.17.21.
    - [Release notes](https://github.com/lodash/lodash/releases)
    - [Commits](https://github.com/lodash/lodash/compare/4.17.15...4.17.21)
    ---
    updated-dependencies:
    - dependency-name: lodash
2022-09-19 Bump node-fetch from 2.6.0 to 2.6.7 in /software/GoogleCLoud/printGraph
    Bumps [node-fetch](https://github.com/node-fetch/node-fetch) from 2.6.0 to 2.6.7.
    - [Release notes](https://github.com/node-fetch/node-fetch/releases)
    - [Commits](https://github.com/node-fetch/node-fetch/compare/v2.6.0...v2.6.7)
    ---
    updated-dependencies:
    - dependency-name: node-fetch
2022-09-19 Bump node-forge and firebase-admin in /software/GoogleCLoud/printGraph
    Bumps [node-forge](https://github.com/digitalbazaar/forge) and [firebase-admin](https://github.com/firebase/firebase-admin-node). These dependencies needed to be updated together.
    Updates `node-forge` from 0.7.4 to 1.3.1
    - [Release notes](https://github.com/digitalbazaar/forge/releases)
    - [Changelog](https://github.com/digitalbazaar/forge/blob/main/CHANGELOG.md)
    - [Commits](https://github.com/digitalbazaar/forge/compare/0.7.4...v1.3.1)
    Updates `firebase-admin` from 8.9.2 to 11.0.1
2022-10-20 default calculation of decharge curve added
2022-10-20 timer bug fixed
2022-10-21 temp. fix for battery level in uplinkformatter added
2022-10-23 timeSchedule class bug fixed
2022-10-30 Ide setup and compile instructions.
2022-11-13 Bump minimatch from 3.0.4 to 3.1.2 in /software/GoogleCLoud/printGraph
    Bumps [minimatch](https://github.com/isaacs/minimatch) from 3.0.4 to 3.1.2.
    - [Release notes](https://github.com/isaacs/minimatch/releases)
    - [Commits](https://github.com/isaacs/minimatch/compare/v3.0.4...v3.1.2)
    ---
    updated-dependencies:
    - dependency-name: minimatch
2022-12-15 Bump express from 4.17.1 to 4.18.2 in /software/GoogleCLoud/printGraph
    Bumps [express](https://github.com/expressjs/express) from 4.17.1 to 4.18.2.
    - [Release notes](https://github.com/expressjs/express/releases)
    - [Changelog](https://github.com/expressjs/express/blob/master/History.md)
    - [Commits](https://github.com/expressjs/express/compare/4.17.1...4.18.2)
    ---
    updated-dependencies:
2022-12-28 chrono implementation finished
2023-03-04 Bump minimist and mkdirp in /software/GoogleCLoud/printGraph
    Bumps [minimist](https://github.com/minimistjs/minimist) and [mkdirp](https://github.com/isaacs/node-mkdirp). These dependencies needed to be updated together.
    Updates `minimist` from 0.0.8 to 1.2.8
    - [Release notes](https://github.com/minimistjs/minimist/releases)
    - [Changelog](https://github.com/minimistjs/minimist/blob/main/CHANGELOG.md)
    - [Commits](https://github.com/minimistjs/minimist/compare/v0.0.8...v1.2.8)
    Updates `mkdirp` from 0.5.1 to 0.5.6
2023-07-12 Bump semver from 5.7.1 to 5.7.2 in /software/GoogleCLoud/printGraph
    Bumps [semver](https://github.com/npm/node-semver) from 5.7.1 to 5.7.2.
    - [Release notes](https://github.com/npm/node-semver/releases)
    - [Changelog](https://github.com/npm/node-semver/blob/v5.7.2/CHANGELOG.md)
    - [Commits](https://github.com/npm/node-semver/compare/v5.7.1...v5.7.2)
    ---
    updated-dependencies:
2023-07-19 Bump word-wrap from 1.2.3 to 1.2.4 in /software/GoogleCLoud/printGraph
    Bumps [word-wrap](https://github.com/jonschlinkert/word-wrap) from 1.2.3 to 1.2.4.
    - [Release notes](https://github.com/jonschlinkert/word-wrap/releases)
    - [Commits](https://github.com/jonschlinkert/word-wrap/compare/1.2.3...1.2.4)
    ---
    updated-dependencies:
    - dependency-name: word-wrap
2023-07-26 main class started
2023-08-26 LoRaConnector class started
2023-08-27 status logger: first version finished
2023-08-30 LoRaConnector finished
2023-09-02 new bikeCounter class continued
2023-09-12 BikeCounter main class continued
2023-10-03 Bump debug from 4.1.1 to 4.3.4 in /software/GoogleCLoud/printGraph
    Bumps [debug](https://github.com/debug-js/debug) from 4.1.1 to 4.3.4.
    - [Release notes](https://github.com/debug-js/debug/releases)
    - [Commits](https://github.com/debug-js/debug/compare/4.1.1...4.3.4)
    ---
    updated-dependencies:
    - dependency-name: debug
2023-10-14 first compilable version of refactored code
2023-11-21 mkrwan_v2 submodule moved to src folder
2023-11-25 time sync finished
2023-11-25 motion and logger bugs fixed
2023-11-25 mkrwan_v2 submodule removed
2023-11-25 RSSI and SNR to database dump added
2023-11-26 google cloud function updated to support the device-trail connection collection
2023-12-02 PIR shutdown and error handling improved
2023-12-03 google cloud function updated to store the whole payload
2023-12-04 Bump @google-cloud/firestore and firebase-admin
    Bumps [@google-cloud/firestore](https://github.com/googleapis/nodejs-firestore) to 6.8.0 and updates ancestor dependency [firebase-admin](https://github.com/firebase/firebase-admin-node). These depen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
    Updates `@google-cloud/firestore` from 3.5.1 to 6.8.0
    - [Release notes](https://github.com/googleapis/nodejs-firestore/releases)
    - [Changelog](https://github.com/googleapis/nodejs-firestore/blob/main/CHANGELOG.md)
    - [Commits](https://github.com/googleapis/nodejs-firestore/compare/v3.5.1...v6.8.0)
    Updates `firebase-admin` from 8.9.2 to 11.11.1
2023-12-07 ci job yml updated
2023-12-07 gtest bugs fixed
2023-12-07 motion interrupt bug fixed
2023-12-09 pcb v0.2 started
2023-12-29 statusLogger bug fixed and debug output removed
2024-01-03 timer interval bug fixed
2024-03-22 Gerber files added and BOM started
2024-03-23 old gerber files removed and BOM updated
2024-04-24 schematic pdf's created
2024-06-15 hal started
2024-06-16 deepSleep moved to hal class
2024-06-16 Arduino deps. removed from bikeCounter.hpp
2024-06-16 remaining hw interaction moved to hal class
2024-06-22 sw and hw version updated
2024-07-14 Google cloud function gateway eui bug fixed (credits to Guido)
2025-01-22 initial setup of stm32 project
2025-01-22 bikecounter source files copied
2025-03-02 stm project changed from c to cpp
2026-01-06 Refactor downlink request example to use Swisscom API and encode time drift payload
2026-01-06 Added auth to downlink example.
2026-03-01 Some refactrong to make code more readable.
2026-03-08 Added working downlink code to function.
